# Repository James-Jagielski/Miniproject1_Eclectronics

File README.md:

# Miniproject1_Eclectronics
This is a readme

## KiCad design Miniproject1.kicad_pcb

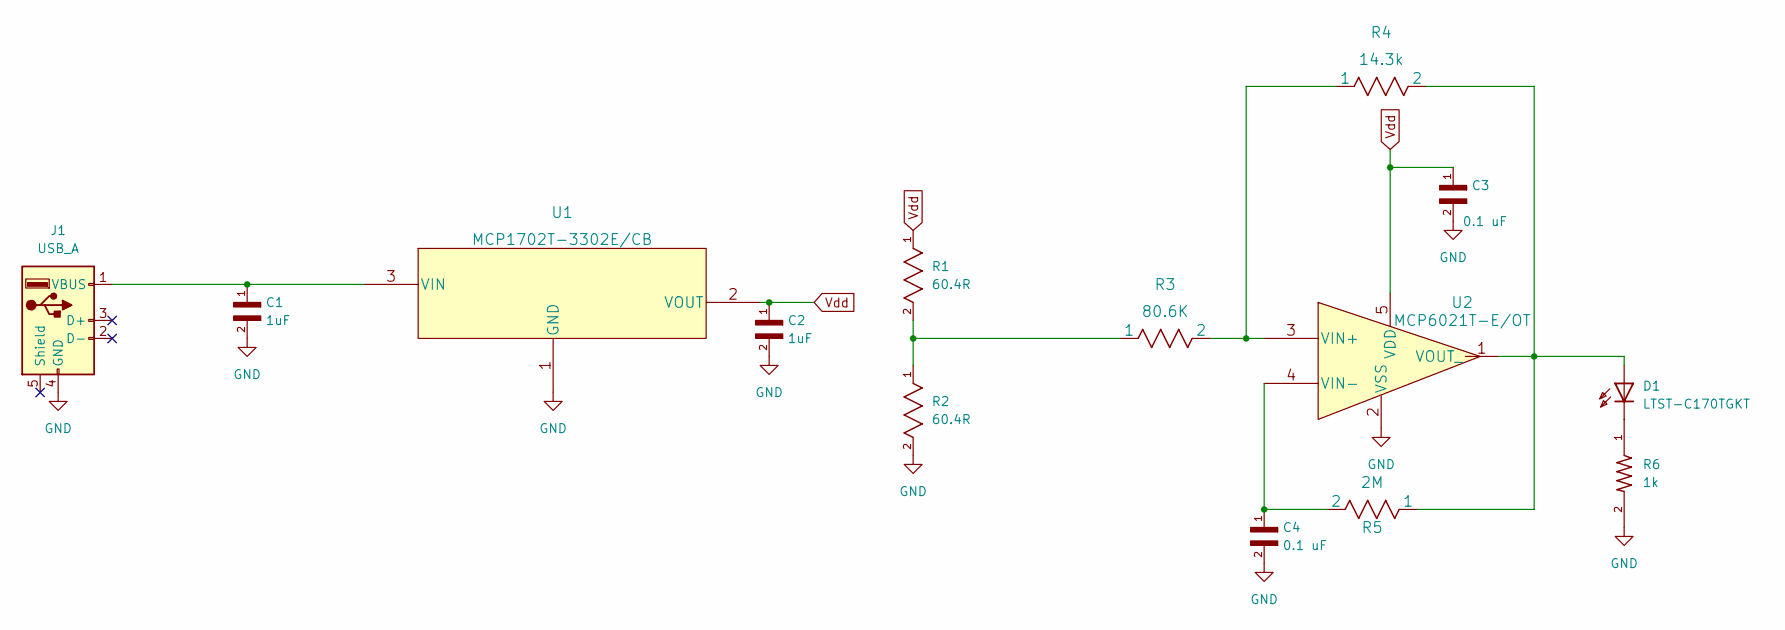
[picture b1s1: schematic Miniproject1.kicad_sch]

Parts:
C1, C2: 1uF
C3, C4: 0.1 uF; .1uF
D1: LTST-C170TGKT; DIOC200X125X110(LED_Green)
J1: USB_A; USB-A
R1, R2: 60.4R; TOLERANCE ±1%; MPN RC0603FR-0760R4L
R3: 80.6K; 80.6k
R4: 14.3k
R5: 2M
R6: 1k
U1: MCP1702T-3302E/CB; MCP1702T-3302E&slash_CB (volt_reg)
U2: MCP6021T-E/OT; MCP6021T-E&slash_OT(op-amp)

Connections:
GND: C1.2, C2.2, C3.2, C4.2, J1.4 (GND), R2.2, R6.2, U1.1 (GND), U2.2 (VSS)
unnamed: C1.1, J1.1 (VBUS), U1.3 (VIN)
unnamed: C4.1, R5.2, U2.4 (VIN-)
unnamed: D1.+, R4.2, R5.1, U2.1 (VOUT_)
unnamed: D1.-, R6.1
unnamed: R1.2, R2.1, R3.1
unnamed: R3.2, R4.1, U2.3 (VIN+)
Vdd: C2.1, C3.1, R1.1, U1.2 (VOUT), U2.5 (VDD)

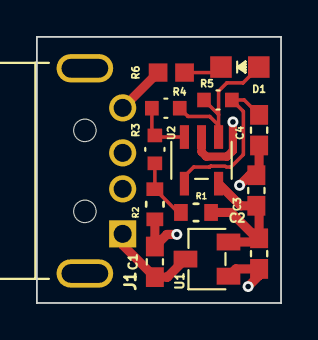
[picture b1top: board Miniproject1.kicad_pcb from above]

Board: 2 copper layers, 13.6 x 14.8 mm, 14 parts (0 on the bottom side), 8 nets.

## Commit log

2022-09-16 figure folder to repo
2022-09-16 KiCad parts
2022-09-16 project files
    Schematic and layout of the PCB
2022-09-16 MATLAB items
2022-09-16 LTspice items

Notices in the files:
parts and their libraries:
Copyright 2021 Accelerated Designs. All rights reserved.
